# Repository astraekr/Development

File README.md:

# PrivateDev
University and home work. Mostly WIP

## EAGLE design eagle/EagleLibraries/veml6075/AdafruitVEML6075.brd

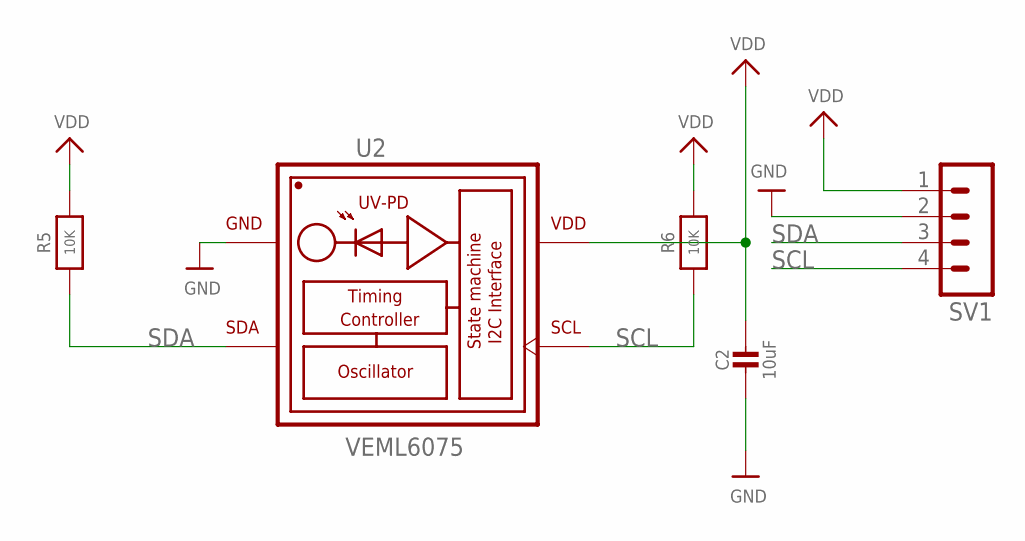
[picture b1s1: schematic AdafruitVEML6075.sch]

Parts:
C2: 10uF; 0805-NO
R5, R6: 10K; 0805-NO
SV1: MA04-1
U2: VEML6075; VISHAY_VEML6075_1.25X2X1

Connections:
GND: C2.2, SV1.2, U2.1 (GND)
SCL: R6.1, SV1.4, U2.3 (SCL)
SDA: R5.1, SV1.3, U2.2 (SDA)
VDD: C2.1, R5.2, R6.2, SV1.1, U2.4 (VDD)

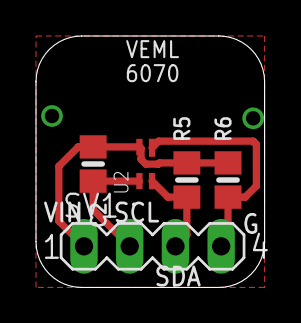
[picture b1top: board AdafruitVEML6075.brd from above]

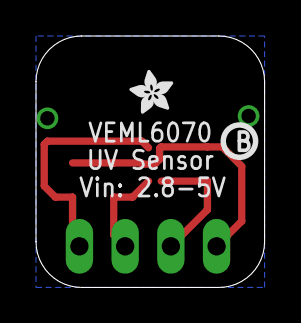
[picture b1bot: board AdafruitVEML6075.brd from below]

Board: 2 copper layers, 12.7 x 14.0 mm, 7 parts (2 on the bottom side), 4 nets.

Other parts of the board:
U$2: PCBFEAT-REV-040
U$14: ADAFRUIT_2.5MM

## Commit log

2017-08-02 Initial commit of development directory
2017-08-02 Delete README.md
    In order to allow for commit from local repo
2017-08-04 Libuvc code from: http://answers.opencv.org/question/93848/problem-black-image/ to test libuvc functionality with boson. Code builds but no output yet
2017-08-04 Find device parameters adjusted to prevent filtering. Webcam now found
2017-08-08 Unresolved issue with uvc_get_stream_ctrl_format_size
2017-08-08 Stream control setting successful. Output still useless
2017-09-11 GetBoson now streams pre-AGC video
2017-09-13 Takes and saves an image with keyboard prompt. Hacky.
2017-09-13 Added program to average pixel values, and take one pic at a time

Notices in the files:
parts and their libraries:
microbuilder: This work is placed in the public domain, and may be freely used for commercial and non-commercial work with the following conditions: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
